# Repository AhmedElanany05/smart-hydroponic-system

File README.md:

# Smart Hydroponic System

**A vertical hydroponic tower for strawberries that spots plant diseases with a camera and AI, and adjusts nutrient dosing automatically.**

Bachelor project · Ahmed Mohamed Elanany

<p align="center">
  
  &nbsp;&nbsp;
  
</p>

---

## The idea

Plant diseases spread fast in hydroponic systems, and people often notice them too late. This system checks the plants with a camera all the time. When the AI model sees disease or anything unusual on a plant, it triggers the nutrient dosing pumps automatically.

## How it works

```mermaid
flowchart LR
CAM["USB camera"] --> J["Jetson Orin Nano<br/>YOLO11n + TensorRT"]
J -->|"Wi-Fi commands"| E["ESP32 on custom PCB"]
S["Sensors<br/>pH, TDS, temperature,<br/>water level"] --> E
E --> D["Nutrient dosing pumps"]
E --> P["Tower pump"]
P -->|"water up the central pipe"| T["Hydroponic tower<br/>strawberries"]
D --> T
SUN["Solar panel + 12 V battery"] --> E
```

1. **Watch:** a camera monitors the strawberry plants in the tower.
2. **Detect:** a YOLO11n model on the Jetson Orin Nano checks each image for signs of disease.
3. **Act:** the ESP32 controller switches the nutrient dosing pumps and the tower pump, and turns the Jetson on only when it is needed.
4. **Power:** everything runs from a solar panel and a 12 V battery.

## Tower design (SolidWorks)

- **Modular:** twist-lock modules that stack on top of each other, so the tower can grow or be repaired one section at a time.
- **Top-feed water system:** water rises through a central pipe and is spread from the head to every module.
- **Every plant is independent:** each pocket gets water directly, so lower plants never depend on the plants above them.
- **Semi-hydroponic pockets:** plants sit in pots with growing medium, designed so water flows through every plant without blocking.

The twist-lock concept is based on an open-source modular tower design (Modular Hydroponic Tower Garden REMASTERED).

## PCB design

I design my own PCBs. The tower controller board was designed from scratch in **KiCad**: schematic, layout, custom footprints and manufacturing files.

- Two-layer through-hole board, 150 × 160 mm
- 12 V battery input with reverse-polarity protection (P-MOSFET), TVS diode and a fuse for each branch
- Three MOSFET-switched pump outputs and a high-side switch for the Jetson
- ESP32 socket, ADS1115 ADC for pH, TDS and battery voltage, connectors for all sensors
- Mount for an XL4015 buck module (5 V)
- Hardware dry-run protection: the low-water float switch blocks the tower pump even if the software tries to run it

Files: [`pcb/`](pcb) (KiCad project, schematic PDF, parts list, Gerbers).

## AI model

| | |
| --- | --- |
| Model | YOLO11n, trained on 9 strawberry disease / healthy classes |
| Accuracy | mAP50 **0.881** on the test split |
| Jetson Orin Nano | TensorRT FP16, about **12 ms** per image |

Details: [`ai/results.md`](ai/results.md).

## Repository

| Folder | What is inside |
| --- | --- |
| [`esp32/`](esp32) | ESP32 firmware for the tower controller (Arduino), sensor test sketches and wiring notes |
| [`jetson/`](jetson) | Jetson ↔ ESP32 link test |
| [`ai/`](ai) | Training notebook (Google Colab), training results and the trained weights |
| [`sim/`](sim) | MATLAB scripts and the Simulink model (solar energy, battery, water flow, tank) |
| [`pcb/`](pcb) | KiCad files of the tower controller board |
| [`images/`](images) | Pictures used in this README |

## Tech

| Area | Tools |
| --- | --- |
| AI / vision | Python, YOLO11n, TensorRT, NVIDIA Jetson Orin Nano |
| Embedded | ESP32 (C/C++, Arduino), Wi-Fi web interface, ADS1115 |
| PCB design | KiCad |
| Mechanical design | SolidWorks |
| Simulation | MATLAB / Simulink |
| Power and pumps | Solar panel, 12 V battery, tower pump, nutrient dosing pumps |

## Status

In development: the controller board is built and in testing, the AI model runs on the Jetson, and the tower is being prepared for printing.

## Author

**Ahmed Mohamed Elanany** · [LinkedIn](https://www.linkedin.com/in/ahmed-elanany) · ahmedelanany34@gmail.com

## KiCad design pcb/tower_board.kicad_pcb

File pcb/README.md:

# Tower controller board (v1.1)

Two-layer through-hole board, 150 × 160 mm, made in KiCad 10.
It takes the 12 V battery, protects and fuses it, switches the three pumps and the Jetson, carries the ESP32 (NodeMCU-32S, 38-pin) with all sensor connectors, and has a mounting place for the XL4015 buck module.

## Files

| File | What it is |
|---|---|
| `tower_board.kicad_pro` | KiCad project (open this) |
| `tower_board.kicad_sch` | Schematic, one A3 sheet |
| `tower_board.kicad_pcb` | Board layout |
| `tower.pretty/` | Custom footprints: BLX-A fuse holder, XL4015 module mount |
| `manufacturing/tower_board_gerbers.zip` | Gerbers + drill files (plated and non-plated), send this to the PCB shop |
| `manufacturing/tower_board.step` | 3D model of the board for SolidWorks |
| `docs/tower_board_schematic.pdf` | Schematic as PDF |
| `docs/tower_board_bom.csv` | Parts list |
| `docs/board_1to1_print.pdf` | Actual-size print for checking the parts before ordering |
| `docs/board_3d_*.png` | 3D renders |

## Board summary

| Block | Parts | Notes |
|---|---|---|
| Battery input | J1, Q1 (IRF4905), R1, D1, D2 (P6KE18A), C1, C2 | Reverse-polarity protection with a P-MOSFET, TVS against spikes |
| Fuses | F1 1 A tower pump, F2 1 A nutrient pumps, F3 5 A Jetson, F4 2 A buck | 5×20 mm glass fuses |
| Tower pump | J2, Q2 (IRLZ44N), D3, R5, R6, R7, LED2 | Low-side switch, ESP32 IO25 |
| Nutrient pump A | J3, Q3, D5, R8, R9, R10, LED3 | ESP32 IO26 |
| Nutrient pump B | J4, Q4, D6, R11, R12, R13, LED4 | ESP32 IO27 |
| Jetson | J5, Q5 (IRF4905), Q6 (PN2222A), R14–R18, C4, LED5 | High-side switch, ESP32 IO13 (high = Jetson on) |
| 5 V | J6 → XL4015 module (M1) → J7, D7, C5–C8, L1, D8, LED6 | 5 V for the ESP32 (through D8) and a filtered 5 V for the sensors |
| ESP32 | J8, J9 (2 × 19-pin sockets, 22.86 mm apart) | NodeMCU-32S, 38-pin |
| ADS1115 | J10 (10-pin socket) | Address 0x48, runs on 3.3 V |

## ESP32 pin map

| GPIO | Use | GPIO | Use |
|---|---|---|---|
| 25 | Tower pump | 21 / 22 | I2C SDA / SCL (ADS1115, I2C header) |
| 26 | Nutrient pump A | 4 | DS18B20 (4.7 k pull-up on board) |
| 27 | Nutrient pump B | 19 | DHT11 (10 k pull-up on board) |
| 13 | Jetson power | 5 / 18 | HC-SR04 trigger / echo (echo divided 1 k / 2 k) |
| 32 | Float switch LOW | 34 | Leak sensor (analog) |
| 33 | Float switch HIGH | 14, 23, 35, 36 | Free, on the expansion header |

Power: the board feeds the ESP32 on its **5V** pin (through D8) and takes 3.3 V from its **3V3** pin for the sensors.
ADS1115 inputs: A0 = pH (10 k / 20 k divider), A1 = TDS, A2 = battery voltage (68 k / 18 k, so V_bat = V_A2 × 4.78), A3 = free on the expansion header.

## XL4015 buck module

The module (66 × 39 mm, with voltmeter display) screws onto the board at M1 with four M3 screws and 10 mm standoffs, display side up.
Wires: **J6 BUCK IN → module IN**, **module OUT → J7 5V IN**, red to "+", black to "−".
Set the output to **5.0 V** (voltage knob) and the current limit to about **1.5 A** (current knob) before connecting J7.

## Dry-run protection

The LOW float switch also pulls the tower pump gate down through D4, so the tower pump cannot run when the tank is low, even if the software tries to turn it on.
For this to work, the LOW float switch must be **closed when the water is low**. Most float switches can be flipped on their stem to get this.

## Check before ordering (print `docs/board_1to1_print.pdf` at 100 %)

1. **ESP32 board:** the two socket rows are 22.86 mm apart (centre to centre), for the NodeMCU-32S.
2. **XL4015 holes:** the mount uses 4.2 mm holes on 60 × 33 mm. Lay the module on the print and check that its holes line up.
3. **Fuse holders:** the footprint uses 22.5 mm between the two pins. Measure your BLX-A holders. If they differ, change the pad position in `tower.pretty`.
4. **Screw terminals:** the footprint is for 5.0 mm pitch (KF126 / MX126 type).

## PCB order details

- 2 layers, 1.6 mm FR-4, 1 oz copper, plated through holes, HASL, green mask, white silkscreen.
- Smallest track 0.5 mm, smallest gap 0.3 mm, smallest hole 0.65 mm (vias).
- Ground pour on both layers.

## Assembly order

1. Resistors, diodes (check the band, the "K" mark is the cathode), the inductor.
2. Small capacitors, LEDs (the flat side and square pad are the cathode), Q6.
3. Pin headers and sockets, then the TO-220 MOSFETs.
4. Electrolytic capacitors (the "+" mark and square pad), fuse holders, screw terminals.
5. Standoffs for the XL4015 module.

## First power-up

1. No fuses, no ESP32, no modules. Connect the battery through the 10 A main fuse. The 12 V LED must light.
2. Insert F4 only. Wire J6 to the XL4015 IN and **set it to 5.0 V** before wiring its OUT to J7.
3. Check 5 V on the sensor headers, then plug in the ESP32 and the ADS1115.
4. Insert F1–F3 and test each output with the pump or a 12 V bulb.

## Off the board

- 10 A fuse in an inline holder right at the battery + terminal (and another on the charge controller's + wire).
- 1.5 mm² wire for the battery and the Jetson, 1 mm² is enough for the pumps.
- Pump wiring: red (+) to the "+" side of each terminal, black (−) to the "−" side. The "−" side is switched, so it is not ground.

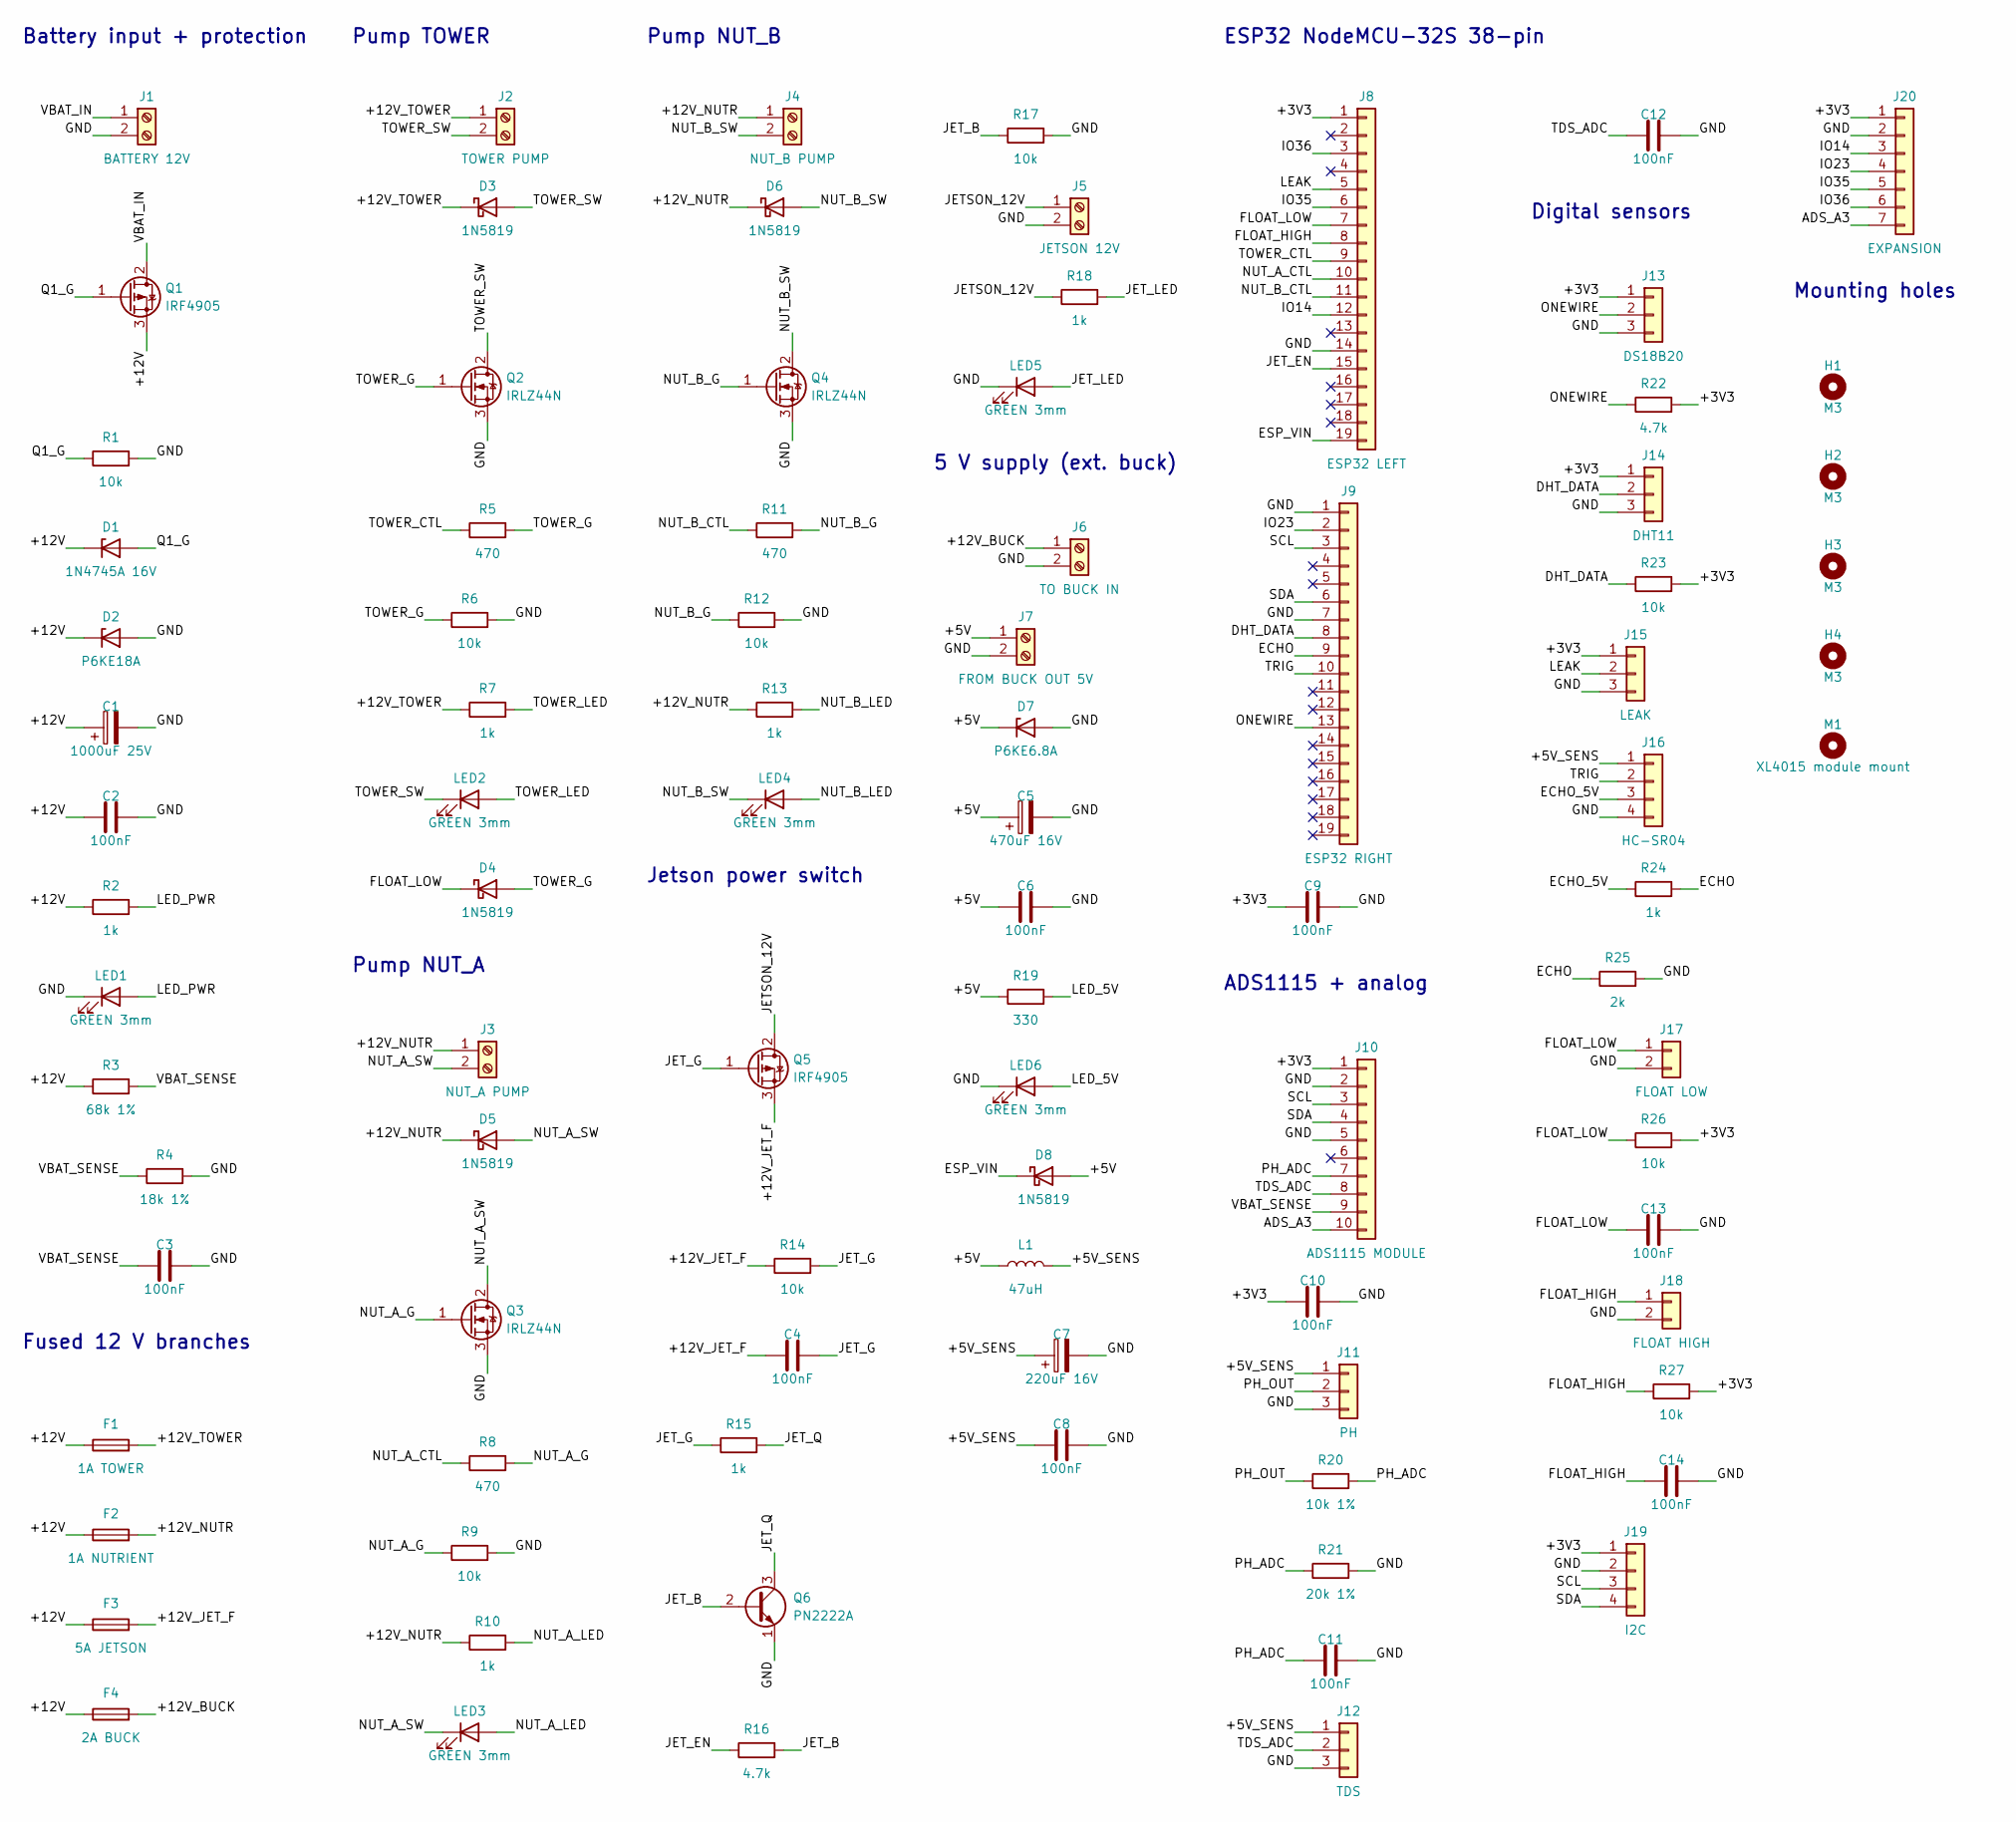
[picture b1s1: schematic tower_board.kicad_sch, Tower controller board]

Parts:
C1: 1000uF 25V; CP_Radial_D12.5mm_P5.00mm
C2, C3, C4, C6, C8, C9, C10, C11, C12, C13, C14: 100nF; C_Disc_D5.0mm_W2.5mm_P5.00mm
C5: 470uF 16V; CP_Radial_D8.0mm_P3.50mm
C7: 220uF 16V; CP_Radial_D6.3mm_P2.50mm
D1: 1N4745A 16V; D_DO-41_SOD81_P10.16mm_Horizontal
D2: P6KE18A; D_DO-15_P12.70mm_Horizontal
D3, D4, D5, D6, D8: 1N5819; D_DO-41_SOD81_P10.16mm_Horizontal
D7: P6KE6.8A; D_DO-15_P12.70mm_Horizontal
F1: 1A TOWER; Fuseholder_5x20_BLX-A
F2: 1A NUTRIENT; Fuseholder_5x20_BLX-A
F3: 5A JETSON; Fuseholder_5x20_BLX-A
F4: 2A BUCK; Fuseholder_5x20_BLX-A
H1, H2, H3, H4: M3; MountingHole_3.2mm_M3
J1: BATTERY 12V; TerminalBlock_MaiXu_MX126-5.0-02P_1x02_P5.00mm
J2: TOWER PUMP; TerminalBlock_MaiXu_MX126-5.0-02P_1x02_P5.00mm
J3: NUT_A PUMP; TerminalBlock_MaiXu_MX126-5.0-02P_1x02_P5.00mm
J4: NUT_B PUMP; TerminalBlock_MaiXu_MX126-5.0-02P_1x02_P5.00mm
J5: JETSON 12V; TerminalBlock_MaiXu_MX126-5.0-02P_1x02_P5.00mm
J6: TO BUCK IN; TerminalBlock_MaiXu_MX126-5.0-02P_1x02_P5.00mm
J7: FROM BUCK OUT 5V; TerminalBlock_MaiXu_MX126-5.0-02P_1x02_P5.00mm
J8: ESP32 LEFT; PinSocket_1x19_P2.54mm_Vertical
J9: ESP32 RIGHT; PinSocket_1x19_P2.54mm_Vertical
J10: ADS1115 MODULE; PinSocket_1x10_P2.54mm_Vertical
J11: PH; PinHeader_1x03_P2.54mm_Vertical
J12: TDS; PinHeader_1x03_P2.54mm_Vertical
J13: DS18B20; PinHeader_1x03_P2.54mm_Vertical
J14: DHT11; PinHeader_1x03_P2.54mm_Vertical
J15: LEAK; PinHeader_1x03_P2.54mm_Vertical
J16: HC-SR04; PinHeader_1x04_P2.54mm_Vertical
J17: FLOAT LOW; PinHeader_1x02_P2.54mm_Vertical
J18: FLOAT HIGH; PinHeader_1x02_P2.54mm_Vertical
J19: I2C; PinHeader_1x04_P2.54mm_Vertical
J20: EXPANSION; PinHeader_1x07_P2.54mm_Vertical
L1: 47uH; L_Axial_L9.5mm_D4.0mm_P12.70mm_Horizontal_Fastron_SMCC
LED1, LED2, LED3, LED4, LED5, LED6: GREEN 3mm; LED_D3.0mm
M1: XL4015 module mount; XL4015_Module_66x39
Q1, Q5: IRF4905; TO-220-3_Vertical
Q2, Q3, Q4: IRLZ44N; TO-220-3_Vertical
Q6: PN2222A; TO-92_Inline_Wide
R1, R6, R9, R12, R14, R17, R23, R26, R27: 10k; R_Axial_DIN0207_L6.3mm_D2.5mm_P10.16mm_Horizontal
R2, R7, R10, R13, R15, R18, R24: 1k; R_Axial_DIN0207_L6.3mm_D2.5mm_P10.16mm_Horizontal
R3: 68k 1%; R_Axial_DIN0207_L6.3mm_D2.5mm_P10.16mm_Horizontal
R4: 18k 1%; R_Axial_DIN0207_L6.3mm_D2.5mm_P10.16mm_Horizontal
R5, R8, R11: 470; R_Axial_DIN0207_L6.3mm_D2.5mm_P10.16mm_Horizontal
R16, R22: 4.7k; R_Axial_DIN0207_L6.3mm_D2.5mm_P10.16mm_Horizontal
R19: 330; R_Axial_DIN0207_L6.3mm_D2.5mm_P10.16mm_Horizontal
R20: 10k 1%; R_Axial_DIN0207_L6.3mm_D2.5mm_P10.16mm_Horizontal
R21: 20k 1%; R_Axial_DIN0207_L6.3mm_D2.5mm_P10.16mm_Horizontal
R25: 2k; R_Axial_DIN0207_L6.3mm_D2.5mm_P10.16mm_Horizontal

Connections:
/+3V3: C9.1, C10.1, J8.1, J10.1, J13.1, J14.1, J15.1, J19.1, J20.1, R22.2, R23.2, R26.2, R27.2
/+5V: C5.1, C6.1, D7.1 (K), D8.2 (A), J7.1, L1.1, R19.1
/+5V_SENS: C7.1, C8.1, J11.1, J12.1, J16.1, L1.2
/+12V: C1.1, C2.1, D1.1 (K), D2.1 (K), F1.1, F2.1, F3.1, F4.1, Q1.3 (S), R2.1, R3.1
/+12V_BUCK: F4.2, J6.1
/+12V_JET_F: C4.1, F3.2, Q5.3 (S), R14.1
/+12V_NUTR: D5.1 (K), D6.1 (K), F2.2, J3.1, J4.1, R10.1, R13.1
/+12V_TOWER: D3.1 (K), F1.2, J2.1, R7.1
/ADS_A3: J10.10, J20.7
/DHT_DATA: J9.8, J14.2, R23.1
/ECHO: J9.9, R24.2, R25.1
/ECHO_5V: J16.3, R24.1
/ESP_VIN: D8.1 (K), J8.19
/FLOAT_HIGH: C14.1, J8.8, J18.1, R27.1
/FLOAT_LOW: C13.1, D4.1 (K), J8.7, J17.1, R26.1
/GND: C1.2, C2.2, C3.2, C5.2, C6.2, C7.2, C8.2, C9.2, C10.2, C11.2, C12.2, C13.2, C14.2, D2.2 (A), D7.2 (A), J1.2, J5.2, J6.2, J7.2, J8.14, J9.1, J9.7, J10.2, J10.5, J11.3, J12.3, J13.3, J14.3, J15.3, J16.4, J17.2, J18.2, J19.2, J20.2, LED1.1 (K), LED5.1 (K), LED6.1 (K), Q2.3 (S), Q3.3 (S), Q4.3 (S), Q6.1 (E), R1.2, R4.2, R6.2, R9.2, R12.2, R17.2, R21.2, R25.2
/IO14: J8.12, J20.3
/IO23: J9.2, J20.4
/IO35: J8.6, J20.5
/IO36: J8.3, J20.6
/JETSON_12V: J5.1, Q5.2 (D), R18.1
/JET_B: Q6.2 (B), R16.2, R17.1
/JET_EN: J8.15, R16.1
/JET_G: C4.2, Q5.1 (G), R14.2, R15.1
/JET_LED: LED5.2 (A), R18.2
/JET_Q: Q6.3 (C), R15.2
/LEAK: J8.5, J15.2
/LED_5V: LED6.2 (A), R19.2
/LED_PWR: LED1.2 (A), R2.2
/NUT_A_CTL: J8.10, R8.1
/NUT_A_G: Q3.1 (G), R8.2, R9.1
/NUT_A_LED: LED3.2 (A), R10.2
/NUT_A_SW: D5.2 (A), J3.2, LED3.1 (K), Q3.2 (D)
/NUT_B_CTL: J8.11, R11.1
/NUT_B_G: Q4.1 (G), R11.2, R12.1
/NUT_B_LED: LED4.2 (A), R13.2
/NUT_B_SW: D6.2 (A), J4.2, LED4.1 (K), Q4.2 (D)
/ONEWIRE: J9.13, J13.2, R22.1
/PH_ADC: C11.1, J10.7, R20.2, R21.1
/PH_OUT: J11.2, R20.1
/Q1_G: D1.2 (A), Q1.1 (G), R1.1
/SCL: J9.3, J10.3, J19.3
/SDA: J9.6, J10.4, J19.4
/TDS_ADC: C12.1, J10.8, J12.2
/TOWER_CTL: J8.9, R5.1
/TOWER_G: D4.2 (A), Q2.1 (G), R5.2, R6.1
/TOWER_LED: LED2.2 (A), R7.2
/TOWER_SW: D3.2 (A), J2.2, LED2.1 (K), Q2.2 (D)
/TRIG: J9.10, J16.2
/VBAT_IN: J1.1, Q1.2 (D)
/VBAT_SENSE: C3.1, J10.9, R3.2, R4.1

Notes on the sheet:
Battery input + protection
Fused 12 V branches
Pump TOWER
Pump NUT_A
Pump NUT_B
Jetson power switch
5 V supply (ext. buck)
ESP32 NodeMCU-32S 38-pin
ADS1115 + analog
Digital sensors
Mounting holes

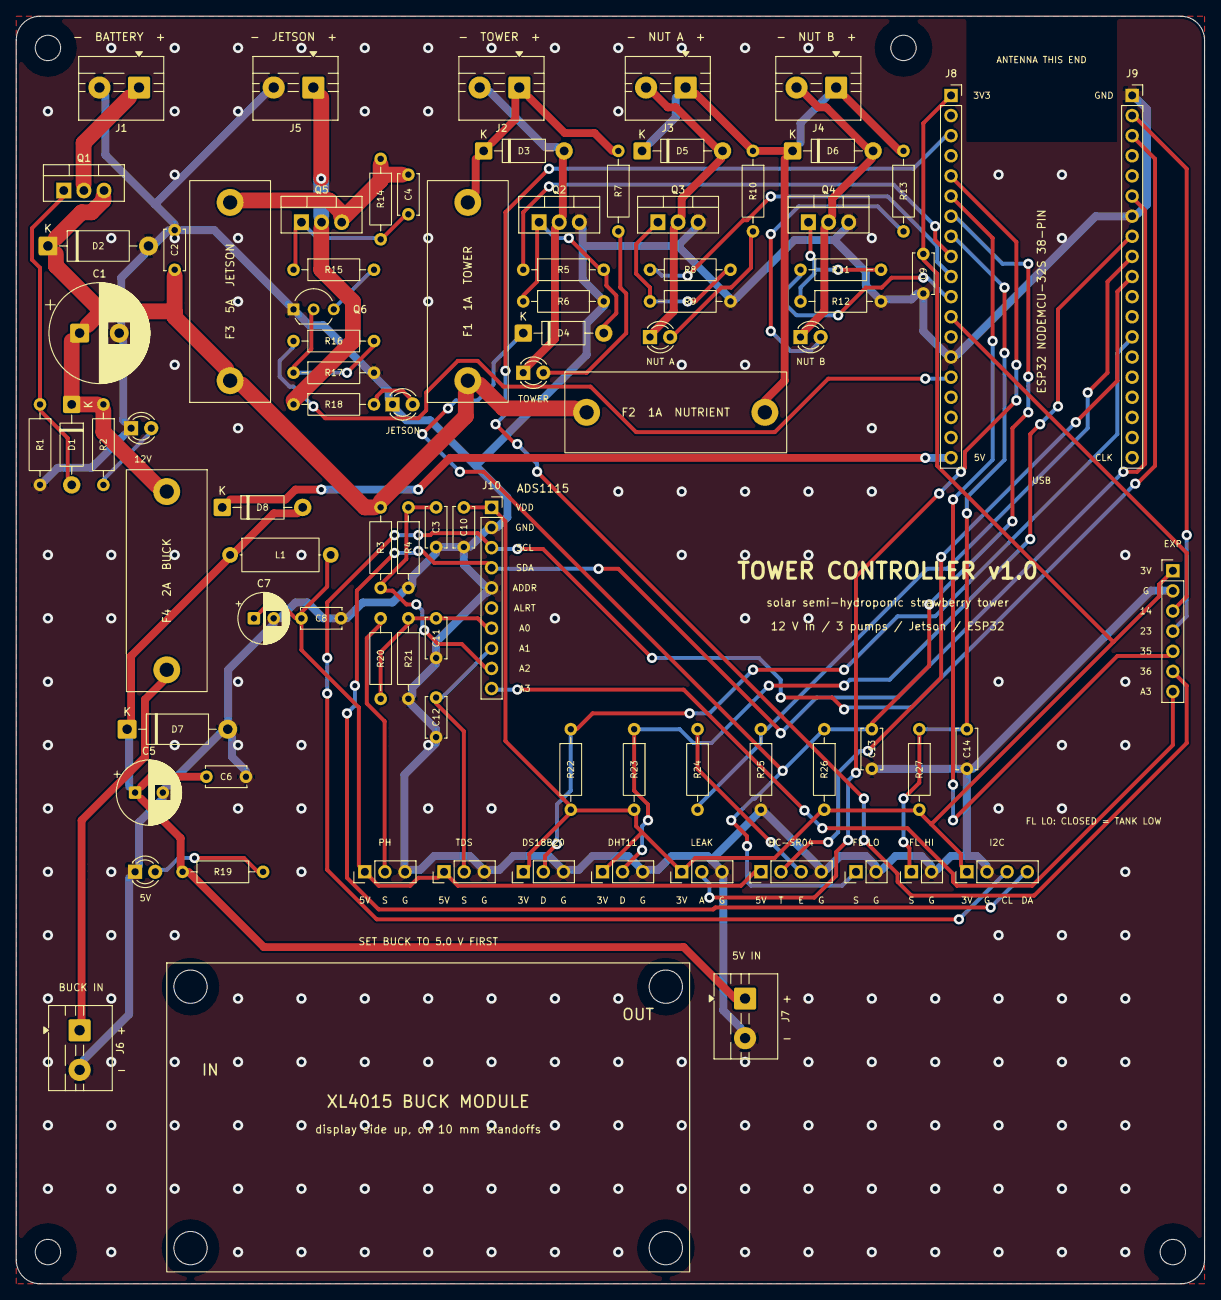
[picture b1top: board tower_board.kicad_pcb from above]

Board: 2 copper layers, 150.0 x 160.0 mm, 91 parts (0 on the bottom side), 51 nets.

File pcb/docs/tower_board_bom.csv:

"Refs","Value","Footprint","Qty"
"C1","1000uF 25V","Capacitor_THT:CP_Radial_D12.5mm_P5.00mm","1"
"C2-C4,C6,C8-C14","100nF","Capacitor_THT:C_Disc_D5.0mm_W2.5mm_P5.00mm","11"
"C5","470uF 16V","Capacitor_THT:CP_Radial_D8.0mm_P3.50mm","1"
"C7","220uF 16V","Capacitor_THT:CP_Radial_D6.3mm_P2.50mm","1"
"D1","1N4745A 16V","Diode_THT:D_DO-41_SOD81_P10.16mm_Horizontal","1"
"D2","P6KE18A","Diode_THT:D_DO-15_P12.70mm_Horizontal","1"
"D3-D6,D8","1N5819","Diode_THT:D_DO-41_SOD81_P10.16mm_Horizontal","5"
"D7","P6KE6.8A","Diode_THT:D_DO-15_P12.70mm_Horizontal","1"
"F1","1A TOWER","tower:Fuseholder_5x20_BLX-A","1"
"F2","1A NUTRIENT","tower:Fuseholder_5x20_BLX-A","1"
"F3","5A JETSON","tower:Fuseholder_5x20_BLX-A","1"
"F4","2A BUCK","tower:Fuseholder_5x20_BLX-A","1"
"J1","BATTERY 12V","TerminalBlock:TerminalBlock_MaiXu_MX126-5.0-02P_1x02_P5.00mm","1"
"J2","TOWER PUMP","TerminalBlock:TerminalBlock_MaiXu_MX126-5.0-02P_1x02_P5.00mm","1"
"J3","NUT_A PUMP","TerminalBlock:TerminalBlock_MaiXu_MX126-5.0-02P_1x02_P5.00mm","1"
"J4","NUT_B PUMP","TerminalBlock:TerminalBlock_MaiXu_MX126-5.0-02P_1x02_P5.00mm","1"
"J5","JETSON 12V","TerminalBlock:TerminalBlock_MaiXu_MX126-5.0-02P_1x02_P5.00mm","1"
"J6","TO BUCK IN","TerminalBlock:TerminalBlock_MaiXu_MX126-5.0-02P_1x02_P5.00mm","1"
"J7","FROM BUCK OUT 5V","TerminalBlock:TerminalBlock_MaiXu_MX126-5.0-02P_1x02_P5.00mm","1"
"J8","ESP32 LEFT","Connector_PinSocket_2.54mm:PinSocket_1x19_P2.54mm_Vertical","1"
"J9","ESP32 RIGHT","Connector_PinSocket_2.54mm:PinSocket_1x19_P2.54mm_Vertical","1"
"J10","ADS1115 MODULE","Connector_PinSocket_2.54mm:PinSocket_1x10_P2.54mm_Vertical","1"
"J11","PH","Connector_PinHeader_2.54mm:PinHeader_1x03_P2.54mm_Vertical","1"
"J12","TDS","Connector_PinHeader_2.54mm:PinHeader_1x03_P2.54mm_Vertical","1"
"J13","DS18B20","Connector_PinHeader_2.54mm:PinHeader_1x03_P2.54mm_Vertical","1"
"J14","DHT11","Connector_PinHeader_2.54mm:PinHeader_1x03_P2.54mm_Vertical","1"
"J15","LEAK","Connector_PinHeader_2.54mm:PinHeader_1x03_P2.54mm_Vertical","1"
"J16","HC-SR04","Connector_PinHeader_2.54mm:PinHeader_1x04_P2.54mm_Vertical","1"
"J17","FLOAT LOW","Connector_PinHeader_2.54mm:PinHeader_1x02_P2.54mm_Vertical","1"
"J18","FLOAT HIGH","Connector_PinHeader_2.54mm:PinHeader_1x02_P2.54mm_Vertical","1"
"J19","I2C","Connector_PinHeader_2.54mm:PinHeader_1x04_P2.54mm_Vertical","1"
"J20","EXPANSION","Connector_PinHeader_2.54mm:PinHeader_1x07_P2.54mm_Vertical","1"
"L1","47uH","Inductor_THT:L_Axial_L9.5mm_D4.0mm_P12.70mm_Horizontal_Fastron_SMCC","1"
"LED1-LED6","GREEN 3mm","LED_THT:LED_D3.0mm","6"
"Q1,Q5","IRF4905","Package_TO_SOT_THT:TO-220-3_Vertical","2"
"Q2-Q4","IRLZ44N","Package_TO_SOT_THT:TO-220-3_Vertical","3"
"Q6","PN2222A","Package_TO_SOT_THT:TO-92_Inline_Wide","1"
"R1,R6,R9,R12,R14,R17,R23,R26,R27","10k","Resistor_THT:R_Axial_DIN0207_L6.3mm_D2.5mm_P10.16mm_Horizontal","9"
"R2,R7,R10,R13,R15,R18,R24","1k","Resistor_THT:R_Axial_DIN0207_L6.3mm_D2.5mm_P10.16mm_Horizontal","7"
"R3","68k 1%","Resistor_THT:R_Axial_DIN0207_L6.3mm_D2.5mm_P10.16mm_Horizontal","1"
"R4","18k 1%","Resistor_THT:R_Axial_DIN0207_L6.3mm_D2.5mm_P10.16mm_Horizontal","1"
"R5,R8,R11","470","Resistor_THT:R_Axial_DIN0207_L6.3mm_D2.5mm_P10.16mm_Horizontal","3"
"R16,R22","4.7k","Resistor_THT:R_Axial_DIN0207_L6.3mm_D2.5mm_P10.16mm_Horizontal","2"
"R19","330","Resistor_THT:R_Axial_DIN0207_L6.3mm_D2.5mm_P10.16mm_Horizontal","1"
"R20","10k 1%","Resistor_THT:R_Axial_DIN0207_L6.3mm_D2.5mm_P10.16mm_Horizontal","1"
"R21","20k 1%","Resistor_THT:R_Axial_DIN0207_L6.3mm_D2.5mm_P10.16mm_Horizontal","1"
"R25","2k","Resistor_THT:R_Axial_DIN0207_L6.3mm_D2.5mm_P10.16mm_Horizontal","1"

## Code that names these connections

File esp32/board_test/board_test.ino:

// Board test: reads every sensor on the PCB every 2 s.
// The ESP32 makes its own Wi-Fi network "Tower-Test" (password towertest). Join it with a phone and open
// http://192.168.4.1 to see the readings. They are also printed on the Serial Monitor (115200 baud).
// Pump buttons on the page run one pump at a time for PUMP_TEST_MS, then switch it off again.
// The J5 (Jetson) button stays on until ALL OFF, for testing J5 with the Jetson or a pump.
// Libraries: "Adafruit ADS1X15" and "DHT sensor library" (already installed for the sensor tests).

#include <Wire.h>
#include <WiFi.h>
#include <WebServer.h>
#include <Adafruit_ADS1X15.h>
#include <DHT.h>

// pins on PCB v1.1 (same as tower_controller/config.h)
// IO13's track is shorted to GND on this board, so J5 is driven from IO33 through a wire to R16
const int PIN_TOWER_PUMP = 25, PIN_NUT_A = 26, PIN_NUT_B = 27, PIN_JETSON = 33;
const int PIN_SOIL = 35, PIN_DHT = 19, PIN_TRIG = 5, PIN_ECHO = 18;
const int PIN_FLOAT_LOW = 32;      // J17, 10k pull-up on the PCB: LOW = switch closed = tank low

const float PH_DIVIDER  = 1.5;    // (10k + 20k) / 20k
const float VBAT_FACTOR = 4.78;   // (68k + 18k) / 18k
const unsigned long PUMP_TEST_MS = 10000;

// J5 is the Jetson output; it is only used here to run a pump while the Jetson is not connected
const int   PUMP_PINS[]  = {PIN_TOWER_PUMP, PIN_NUT_A, PIN_NUT_B, PIN_JETSON};
const char* PUMP_NAMES[] = {"Tower pump (J2)", "Nutrient A (J3)", "Nutrient B (J4)", "J5 output"};
const int   PUMP_COUNT   = 4;
int pumpOn = -1;                   // index of the running pump, -1 = all off
unsigned long pumpStart = 0;

Adafruit_ADS1115 ads;
DHT dht(PIN_DHT, DHT11);
WebServer server(80);
bool adsOk = false;
String report = "starting...";

float adsVolts(int ch) {
  long sum = 0;
  for (int i = 0; i < 8; i++) sum += ads.readADC_SingleEnded(ch);
  return ads.computeVolts((int16_t)(sum / 8));
}

float distanceMm() {
  digitalWrite(PIN_TRIG, LOW);  delayMicroseconds(4);
  digitalWrite(PIN_TRIG, HIGH); delayMicroseconds(10);
  digitalWrite(PIN_TRIG, LOW);
  unsigned long us = pulseIn(PIN_ECHO, HIGH, 30000);
  return us ? us * 0.343 / 2 : -1;
}

void readSensors() {
  char line[64];
  String r;
  if (adsOk) {
    snprintf(line, sizeof line, "Battery : %.2f V\n", adsVolts(2) * VBAT_FACTOR);              r += line;
    snprintf(line, sizeof line, "pH      : module %.3f V\n", adsVolts(0) * PH_DIVIDER);       r += line;
    snprintf(line, sizeof line, "TDS     : %.3f V\n", adsVolts(1));                            r += line;
  } else {
    r += "ADS1115 : NOT FOUND - check that it sits fully in J10\n";
  }
  float t = dht.readTemperature(), h = dht.readHumidity();
  if (isnan(t)) r += "DHT11   : no reading\n";
  else { snprintf(line, sizeof line, "DHT11   : %.1f C, %.0f %%\n", t, h); r += line; }
  float d = distanceMm();
  if (d < 0) r += "HC-SR04 : no echo\n";
  else { snprintf(line, sizeof line, "HC-SR04 : %.0f mm\n", d); r += line; }
  snprintf(line, sizeof line, "Soil    : raw %d\n", analogRead(PIN_SOIL));                    r += line;
  r += digitalRead(PIN_FLOAT_LOW) == LOW ? "Float   : CLOSED (tank low - pump blocked)\n"
                                         : "Float   : open (water OK)\n";
  report = r;
  Serial.println("--------------------------------");
  Serial.print(report);
}

void allPumpsOff() {
  for (int p : PUMP_PINS) digitalWrite(p, LOW);
  pumpOn = -1;
}

void handleRoot() {
  String page =
    "<html><head><meta name=viewport content='width=device-width'><meta http-equiv=refresh content='2;url=/'>"
    "<title>Board test</title></head><body><h3>Tower board test</h3><pre style='font-size:18px'>" + report +
    "Running : " + (pumpOn < 0 ? String("none") : String(PUMP_NAMES[pumpOn])) + "</pre>";
  for (int i = 0; i < PUMP_COUNT; i++)
    page += "<p><a href='/pump?n=" + String(i) + "' style='font-size:22px'>Run " + PUMP_NAMES[i] +
            (i == 3 ? " (stays on)" : " for 10 s") + "</a></p>";
  page += "<p><a href='/off' style='font-size:22px;color:red'>ALL OFF</a></p></body></html>";
  server.send(200, "text/html", page);
}

void handlePump() {
  int n = server.arg("n").toInt();
  allPumpsOff();
  if (n >= 0 && n < PUMP_COUNT) {
    digitalWrite(PUMP_PINS[n], HIGH);
    pumpOn = n;
    pumpStart = millis();
    Serial.printf("%s ON\n", PUMP_NAMES[n]);
  }
  server.sendHeader("Location", "/");
  server.send(303);
}

void handleOff() {
  allPumpsOff();
  server.sendHeader("Location", "/");
  server.send(303);
}

void setup() {
  int outs[] = {PIN_TOWER_PUMP, PIN_NUT_A, PIN_NUT_B, PIN_JETSON};
  for (int p : outs) { digitalWrite(p, LOW); pinMode(p, OUTPUT); }
  pinMode(PIN_TRIG, OUTPUT);
  pinMode(PIN_ECHO, INPUT);
  pinMode(PIN_FLOAT_LOW, INPUT);

  Serial.begin(115200);
  delay(500);
  Wire.begin(21, 22);
  adsOk = ads.begin(0x48);
  if (adsOk) ads.setGain(GAIN_ONE);
  dht.begin();

  WiFi.softAP("Tower-Test", "towertest");
  server.on("/", handleRoot);
  server.on("/pump", handlePump);
  server.on("/off", handleOff);
  server.begin();
  Serial.println("\nBoard test started - Wi-Fi Tower-Test, page http://192.168.4.1");
}

void loop() {
  static unsigned long last = 0;
  server.handleClient();
  // J5 (index 3) stays on until ALL OFF, so a Jetson has time to boot
  if (pumpOn >= 0 && pumpOn != 3 && millis() - pumpStart >= PUMP_TEST_MS) {
    Serial.printf("%s OFF\n", PUMP_NAMES[pumpOn]);
    allPumpsOff();
  }
  if (millis() - last >= 2000) {
    last = millis();
    readSensors();
  }
}
